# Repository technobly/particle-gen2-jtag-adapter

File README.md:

Particle Gen2 JTAG/SWD adapter for Gen3 Debugger
===

Allows you to easily connect a Gen3 Particle Debugger to a Gen2 Photon/Electron in circuit using pass-through headers.

BOM
===

- [1x - J1 - FTSH-105-01-F-DV-K](https://www.digikey.com/product-detail/en/samtec-inc/FTSH-105-01-F-DV-K-TR/SAM13160CT-ND/8827915)
- [8x - R1 ~ R8 (Optional, stuff pull up or pull down for each only if desired) - 10K 0805](https://www.digikey.com/product-detail/en/te-connectivity-passive-product/CRGCQ0805F10K/A129761CT-ND/8577593)
- [2x - J2 - 12-pin stackable header](https://www.digikey.com/product-detail/en/sparkfun-electronics/PRT-14322/1568-1651-ND)

LICENSE
===

CERN OHL v2.0 Permissive - essentially do whatever you want, but if you found this useful [please consider buying me a coffee!](https://buymeacoffee.com/XzUGYrhL3)  Full [LICENSE here](LICENSE)

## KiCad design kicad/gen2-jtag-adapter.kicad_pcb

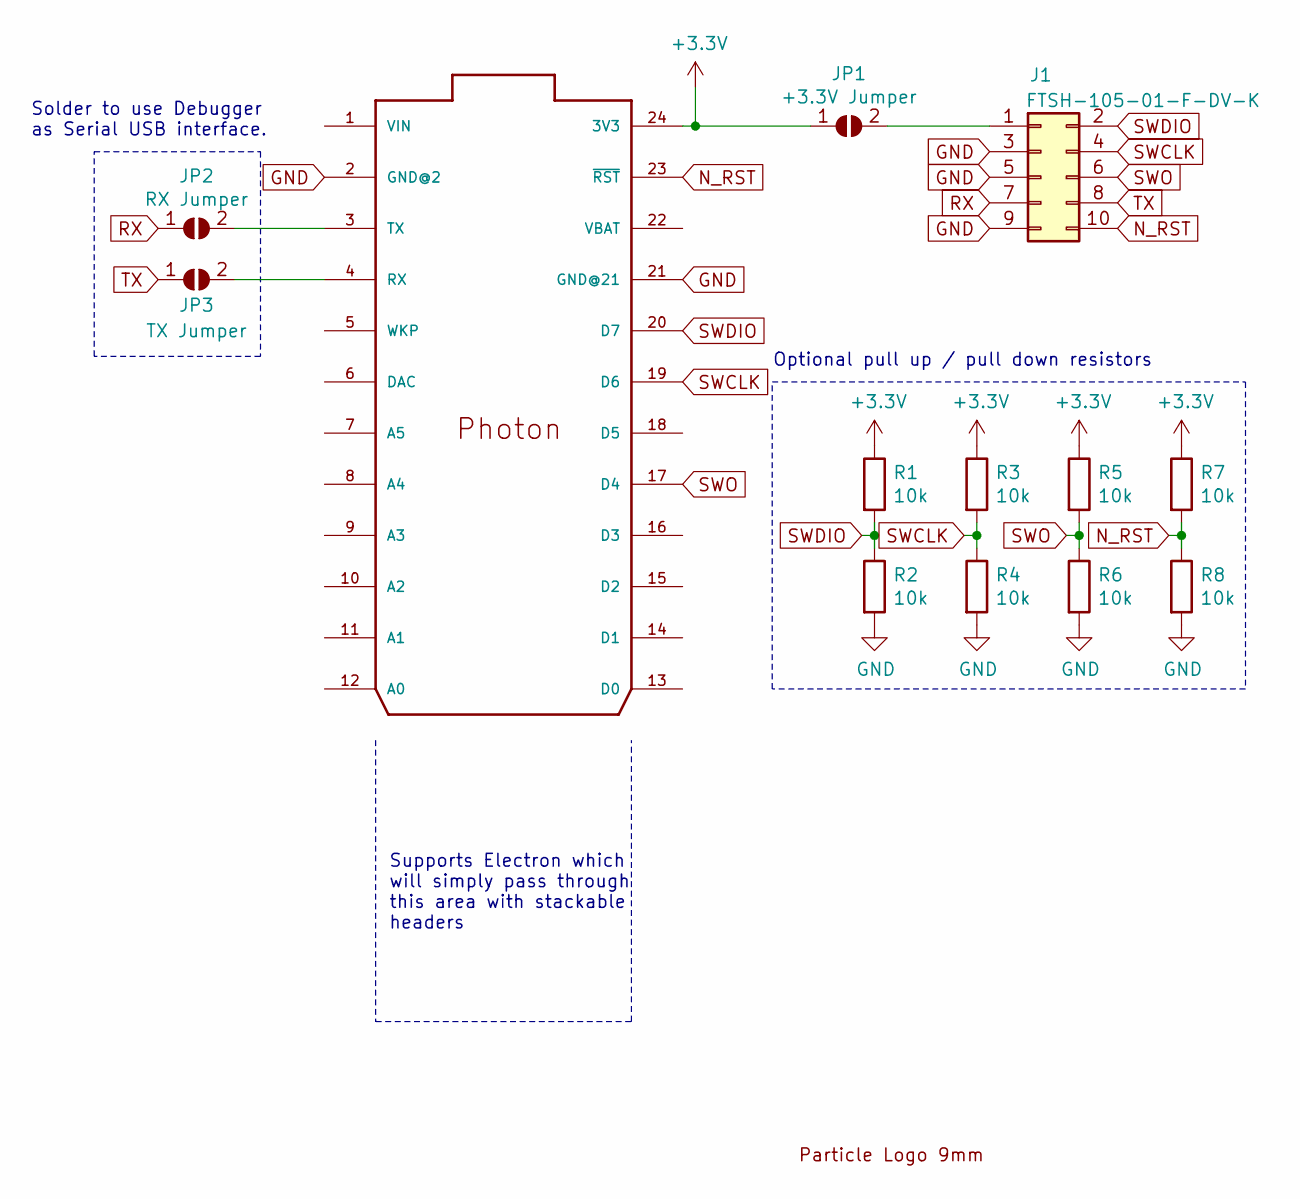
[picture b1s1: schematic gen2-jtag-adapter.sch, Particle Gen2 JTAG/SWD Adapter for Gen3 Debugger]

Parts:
J1: FTSH-105-01-F-DV-K; CONN5X2_1.27
JP1: +3.3V Jumper; SolderJumper-2_P1.3mm_Open_RoundedPad1.0x1.5mm
JP2: RX Jumper; SolderJumper-2_P1.3mm_Open_RoundedPad1.0x1.5mm
JP3: TX Jumper; SolderJumper-2_P1.3mm_Open_RoundedPad1.0x1.5mm
R1, R2, R3, R4, R5, R6, R7, R8: 10k; R_0805_2012Metric_Pad1.15x1.40mm_HandSolder
U1: PHOTON
U2: PARTICLE_LOGO_9MM; particle-logo-9mm

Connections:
+3V3: JP1.1 (A), R1.1, R3.1, R5.1, R7.1, U1.24 (3V3)
GND: J1.3, J1.5, J1.9, R2.2, R4.2, R6.2, R8.2, U1.2 (GND@2), U1.21 (GND@21)
N_RST: J1.10, R7.2, R8.1, U1.23 (~RST~)
unnamed: J1.1, JP1.2 (B)
unnamed: JP2.2 (B), U1.3 (TX)
unnamed: JP3.2 (B), U1.4 (RX)
RX: J1.7, JP2.1 (A)
SWCLK: J1.4, R3.2, R4.1, U1.19 (D6)
SWDIO: J1.2, R1.2, R2.1, U1.20 (D7)
SWO: J1.6, R5.2, R6.1, U1.17 (D4)
TX: J1.8, JP3.1 (A)

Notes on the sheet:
Solder to use Debugger as Serial USB interface.
Optional pull up / pull down resistors
Supports Electron which will simply pass through this area with stackable headers

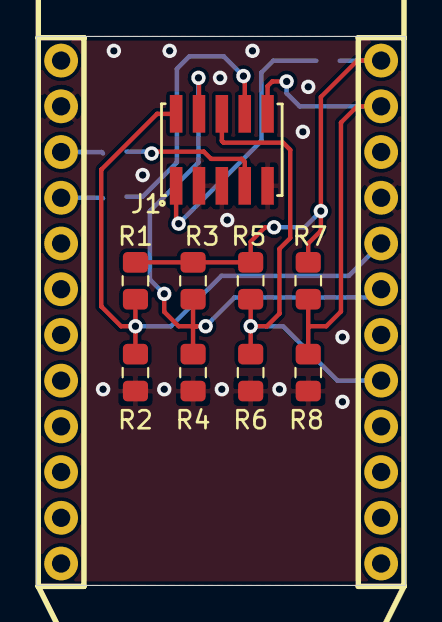
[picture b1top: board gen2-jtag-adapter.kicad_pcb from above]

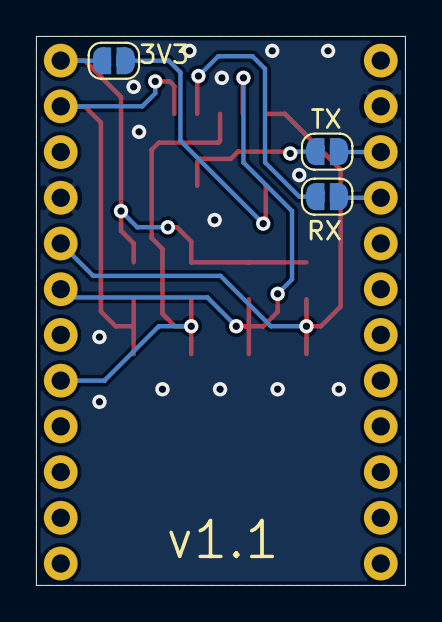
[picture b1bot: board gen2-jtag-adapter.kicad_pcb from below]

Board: 2 copper layers, 20.5 x 30.5 mm, 14 parts (3 on the bottom side), 11 nets.

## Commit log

2020-08-14 initial release v1.0
2020-08-15 added BOM
2020-08-30 updated silkscreen, v1.1
2020-08-30 update render
2020-08-30 add more images
